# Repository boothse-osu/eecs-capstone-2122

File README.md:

# eecs-capstone-2122
Mobile 3D printer project for OSU EECS Capstone 2021-2022

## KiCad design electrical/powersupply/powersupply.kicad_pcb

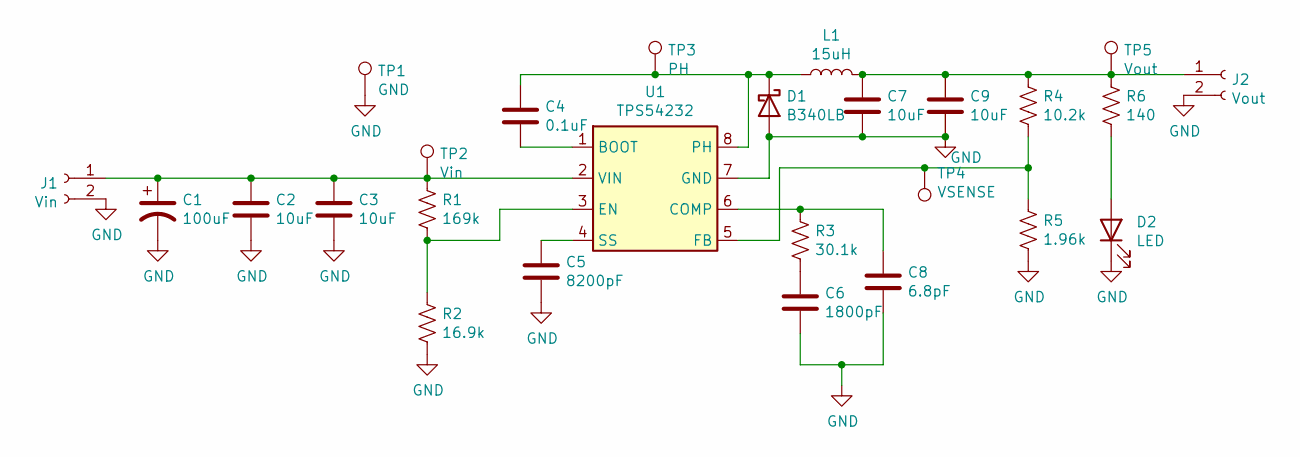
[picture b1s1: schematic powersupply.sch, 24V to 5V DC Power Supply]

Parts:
C1: 100uF; CP_Radial_D6.3mm_P2.50mm
C2, C3: 10uF; C_1210_3225Metric_Pad1.33x2.70mm_HandSolder
C4: 0.1uF; C_0603_1608Metric_Pad1.08x0.95mm_HandSolder
C5: 8200pF; C_0805_2012Metric_Pad1.18x1.45mm_HandSolder
C6: 1800pF; C_0603_1608Metric_Pad1.08x0.95mm_HandSolder
C7, C9: 10uF; C_0805_2012Metric_Pad1.18x1.45mm_HandSolder
C8: 6.8pF; C_0603_1608Metric_Pad1.08x0.95mm_HandSolder
D1: B340LB; D_SMB_Handsoldering
D2: LED; LED_0603_1608Metric_Pad1.05x0.95mm_HandSolder
J1: Vin; PinHeader_1x02_P2.54mm_Vertical
J2: Vout; PinHeader_1x02_P2.54mm_Vertical
L1: 15uH; L_7.3x7.3_H4.5
R1: 169k; R_0805_2012Metric_Pad1.20x1.40mm_HandSolder
R2: 16.9k; R_0805_2012Metric_Pad1.20x1.40mm_HandSolder
R3: 30.1k; R_0805_2012Metric_Pad1.20x1.40mm_HandSolder
R4: 10.2k; R_0805_2012Metric_Pad1.20x1.40mm_HandSolder
R5: 1.96k; R_0805_2012Metric_Pad1.20x1.40mm_HandSolder
R6: 140; R_0805_2012Metric_Pad1.20x1.40mm_HandSolder
TP1: GND; TestPoint_Pad_D1.5mm
TP2: Vin; TestPoint_Pad_D1.5mm
TP3: PH; TestPoint_Pad_D1.5mm
TP4: VSENSE; TestPoint_Pad_D1.5mm
TP5: Vout; TestPoint_Pad_D1.5mm
U1: TPS54232; SOIC-8_3.9x4.9mm_P1.27mm

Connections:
GND: C1.2, C2.2, C3.2, C5.2, C6.2, C7.2, C8.2, C9.2, D1.2 (A), D2.1 (K), J1.2, J2.2, R2.2, R5.2, TP1.1, U1.7 (GND)
unnamed: C1.1, C2.1, C3.1, J1.1, R1.1, TP2.1, U1.2 (VIN)
unnamed: C4.1, D1.1 (K), L1.1, TP3.1, U1.8 (PH)
unnamed: C4.2, U1.1 (BOOT)
unnamed: C5.1, U1.4 (SS)
unnamed: C6.1, R3.2
unnamed: C7.1, C9.1, J2.1, L1.2, R4.1, R6.1, TP5.1
unnamed: C8.1, R3.1, U1.6 (COMP)
unnamed: D2.2 (A), R6.2
unnamed: R1.2, R2.1, U1.3 (EN)
unnamed: R4.2, R5.1, TP4.1, U1.5 (FB)

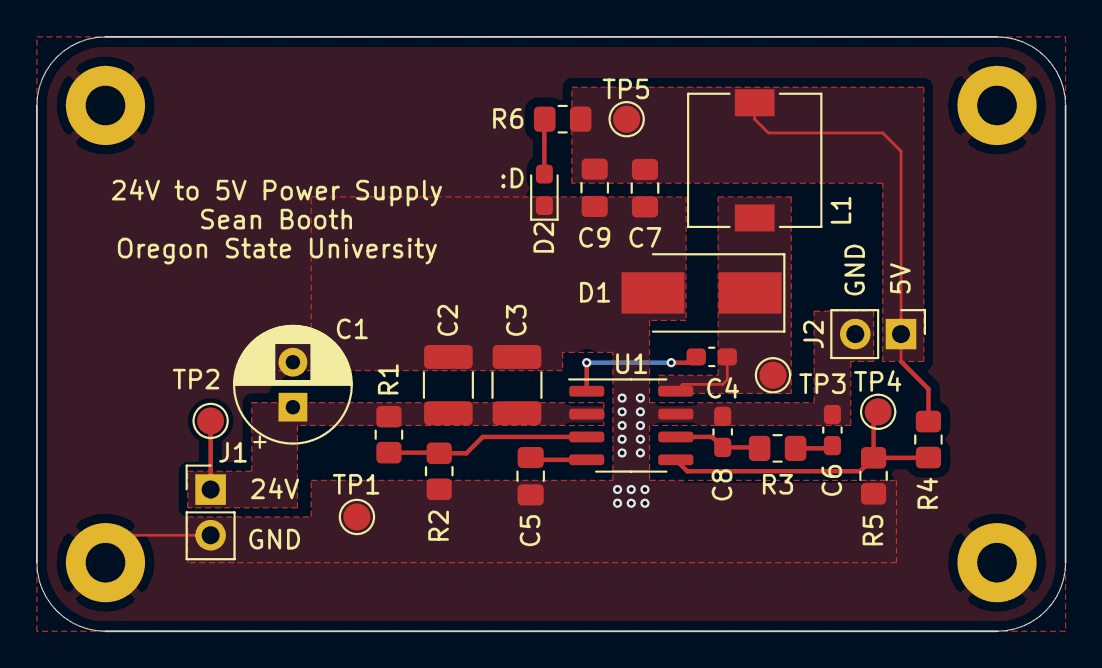
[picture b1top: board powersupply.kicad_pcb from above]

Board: 2 copper layers, 57.1 x 33.0 mm, 26 parts (0 on the bottom side), 11 nets.

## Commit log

2022-01-11 Created VS project. Started very early work on struct.
2022-01-13 Added cglm library and began work on structs
2022-01-16 Forward kinematics, tried to clean up repo
2022-01-16 Re-linked the cglm library in the settings
2022-01-22 Added placeholder for linking
2022-01-22 Initial revision of motor controller circuit
2022-01-22 Begun writing test code for the IK block
2022-01-30 Created test program, finished off inverse kinematics code
2022-01-31 Got test program done, inproved inverse kinematics
2022-02-01 Added a test program for the motor driver and hotend controller
2022-02-10 Added power supply files to repo
2022-02-19 Revised power supply design and completed new PCB layout
2022-02-23 Changed a capacitor part on BOM
2022-02-27 First attempt to remove libraries from github
2022-02-27 Second attempt to remove library
2022-02-27 Removed lib from project, will add info in depedencies
2022-02-28 Wrote CSV parser, most of main program. Waiting on Sam for firmware
2022-02-28 Updated readme to reflect dependencies
2022-02-28 Added dependencies to README.md
2022-02-28 Elaborated on motor controls based on Sam's feedback
2022-02-28 Temporary Firmware.c
2022-02-28 Temporary firmware.h
2022-03-01 Ran the firware functions for the first time
2022-03-01 Fixed issues with main function
2022-03-02 Refactored IK test case to be inncluded in kinematics.h
2022-03-12 Added IK errors for motor bounds, defines file for IK
2022-03-13 Fixed IK bug
2022-03-13 Added new arduino code for running motors on the Nucleo board
2022-03-13 I made changes and forgot what they were...
2022-03-13 Fixes the really nasty stack corruption bug
2022-03-13 Set up motor angle guard test cases
2022-03-14 Auth Test
2022-03-14 C Firmware and Collision Detection Code
2022-03-14 Comment Update
2022-03-14 Interfacing Warning Added
2022-03-14 Added Firmware Block Test Directory
2022-03-14 Updated Test Comments
2022-03-16 Updated all_motors file to use all 5 drivers
2022-04-04 Various changes. I should be commiting more often
2022-04-07 Added extruder test
2022-04-07 Added extruder test code
2022-04-08 Small Error Fixed
2022-04-08 Removed Old Loop from Extruder Test
2022-04-08 Fixed minor error in code
2022-04-10 Began work on USB communication
2022-04-10 Re-added the libraries to the github to make things easier for the MEs
2022-04-10 Improved user experience for toolpath csv file
2022-04-11 Cleaned up more and did some work on the usb communication
2022-04-12 Finished and tested the usb_get_command function
2022-04-14 Finished stylus test
2022-04-14 Added Serial Outputs for Testing Without Printer
2022-04-14 Added More Serial Prints for Testing
2022-04-14 Added controller/computer communication protocol
2022-04-15 Debugged Tests
2022-04-17 Began work on and outlined main printer function
2022-04-19 Wrote more parser and got the usb cpp mess sorted. Untested.
2022-04-21 Communication code can now handle all input codes
2022-04-21 IK data sending code
2022-04-22 Added hotend test code w/ thermal runaway protection
2022-04-27 Firmware and USB Files Added
2022-04-27 Added Stall Detection Files
2022-04-27 Changes to Includes
2022-04-27 Pushed Stall Detection Test Code
2022-04-27 Updated Old Test Files
2022-04-27 Gave Full Stepper Code
2022-04-27 Added Debug Mode
2022-04-27 Added Homing
2022-04-27 Fixed Error in Stall Detection
2022-04-28 Added SLA PIN Test
2022-04-29 Added printer defines and float rounding
2022-04-29 PUSHING ALL FOR PRESTON DEBUGGING
2022-04-29 Homing Deactivated
2022-04-29 Added switch for degrees or radians
2022-04-29 Reworked entire step function
2022-04-29 Changed to readString method for Serial
2022-04-29 Added step-skip protection to homing and removed divide by zero error in move_command
2022-04-29 Updated stall detection method
2022-04-30 Modified hotend test for STM32, non-working due to shared pins with USART2
2022-04-30 Set printer homed position and bugfixes
2022-04-30 Returned Functionallity to Nucleo 64
2022-04-30 Working on debugging IK; saving here
2022-04-30 Error in Step
2022-04-30 Still working through IK bugtesting
2022-05-01 Fixed some IK and the CSV parser
2022-05-01 Yet more IK debug
2022-05-01 Changed variable names and added comments
2022-05-01 Fixed Error that ended up no existing
2022-05-01 Fixed confusing out-dated commented code
2022-05-01 Added extra printer nub
2022-05-02 Mass Push for Sean
2022-05-02 Updated hotend test code for new pins, working as intended
2022-05-02 AAAAAAAAAAAAAAA
2022-05-03 Push for Sean pt. 2
2022-05-03 Integrated hotend code into the main firmware
2022-05-03 Added Jank Extrude Test
2022-05-03 Jank code tends to have errors
2022-05-03 Added temp report command, fixed a couple minor bugs
2022-05-03 Finally got the IK mostly working again
2022-05-03 Verification notes
2022-05-03 Tweaked defines.h for checkoff
2022-05-03 Removed Bad comments and enabled stall detection
2022-05-03 Commented firmware.ino
2022-05-05 Commented Firmware Code
2022-05-12 Added Filament Extrusion
2022-05-12 Added Skeleton Code for Moving Print
2022-05-12 Cleaned up repo a bit
2022-05-19 Code for 6 motors (Needs IK update and PIN Info to function)
2022-05-19 6 Motor Code Successfully Tested with no Z
2022-05-19 Added new stop mode
2022-05-19 Labeled Legacy Code
2022-05-19 Labeled more outdated legacy functions required to interface with IK
2022-05-19 Marked temporary functions for deletion
2022-05-20 Added Delay to Both Move Commands
2022-05-20 Fixed Delay Error
2022-05-26 Pushed Unresponsive 6 MTR Control for Review
2022-05-26 Functional 6 Motor Code
2022-05-26 Adding IK Interfacing Fixes
2022-05-26 Rebuilt the IK to simply use sphere coordinates
2022-05-27 Lots of changes from debug and testing
2022-05-27 Began Re-Write of Move Command
2022-05-27 Finished New Move Command
2022-05-27 Lowered Motor Step Delay
2022-05-27 New Move Command Extrudes When Set to 't'
2022-05-27 Preparing Old Tests for Expo ( Just In Case )
2022-05-27 Set Debug Data Length
2022-05-27 Removedd Stop Message
2022-05-27 Added Data Length Comment
2022-05-31 Rewrote Printing in Firmware
2022-05-31 Moving Handling to firmware.ino
2022-05-31 Adding Time Parameter to Move Command
2022-05-31 Removing Trace of Deleted Functions
2022-05-31 Added Config File for Constants
2022-05-31 Moved Printer Settings to Config.h
2022-05-31 Removed Printer Move
2022-05-31 Removed Constants and Printer Move Function
2022-05-31 Moved Constants to new Config File
2022-06-01 Fixed error with serial communication
2022-06-02 Switched IK to be pre-computed
2022-06-02 Getting ready to debug IK
2022-06-02 Create sloped_star
2022-06-02 Rename sloped_star to sloped_star.csv
2022-06-02 Major Redesign of Printing Loop
2022-06-02 CSV Changes
2022-06-02 IK Settings Set for Sams PC (Port, csv_name)
2022-06-02 Sped up the stuff
2022-06-03 Further gantry speed optimizations
2022-06-03 I don't remember what this was`
